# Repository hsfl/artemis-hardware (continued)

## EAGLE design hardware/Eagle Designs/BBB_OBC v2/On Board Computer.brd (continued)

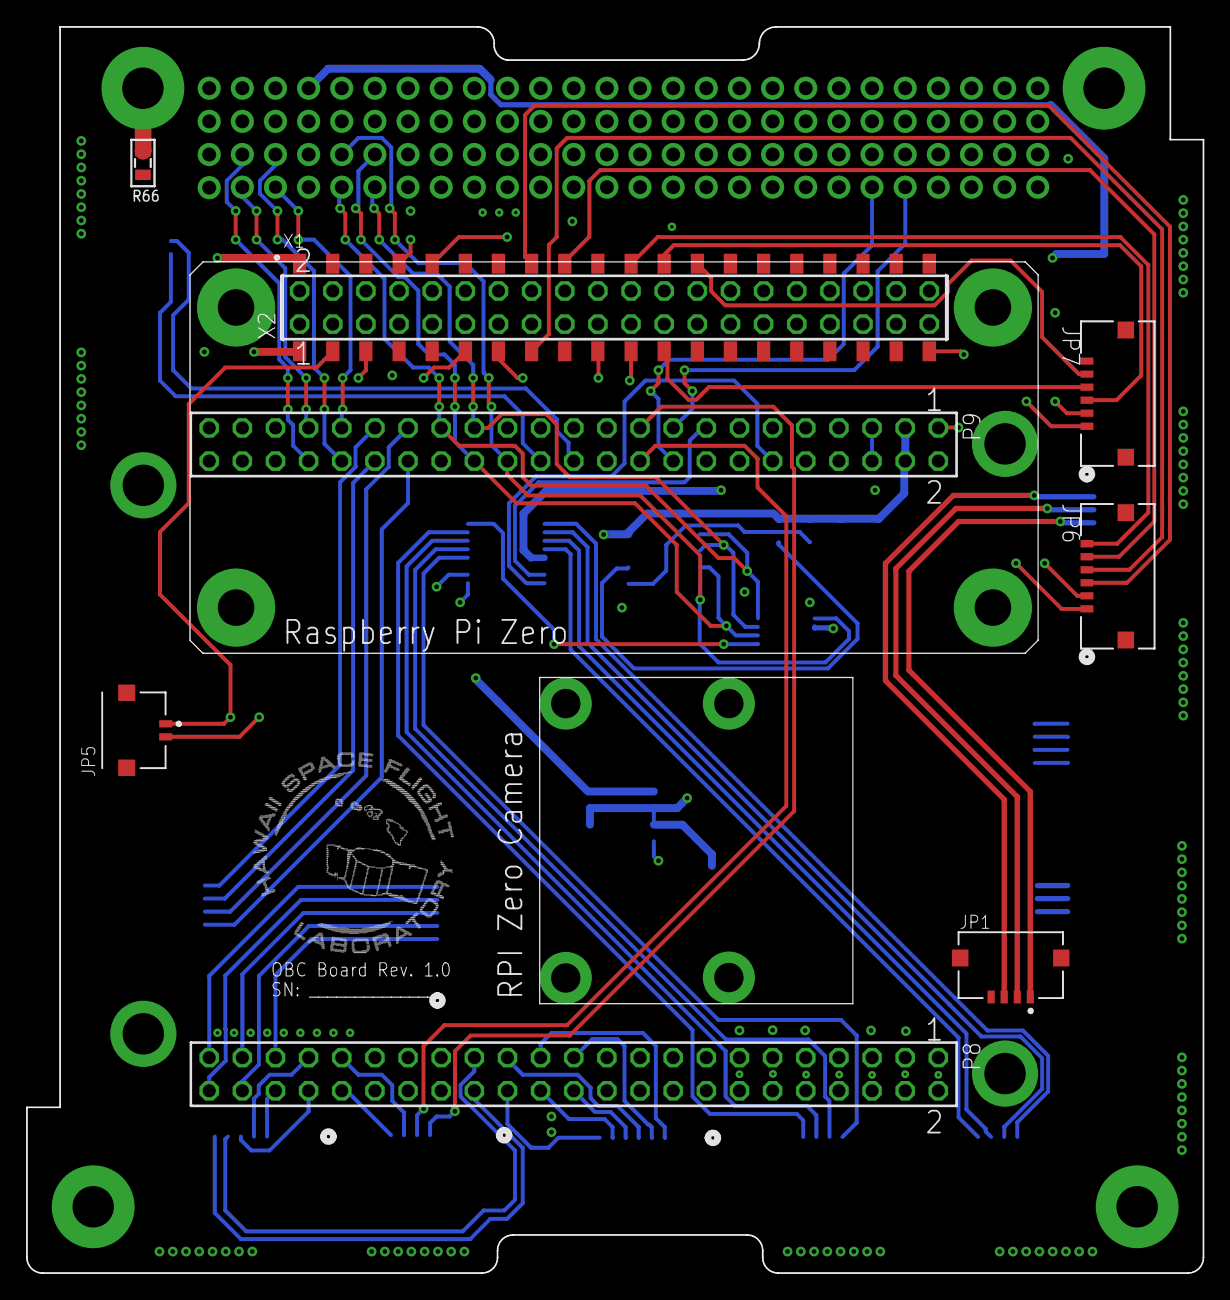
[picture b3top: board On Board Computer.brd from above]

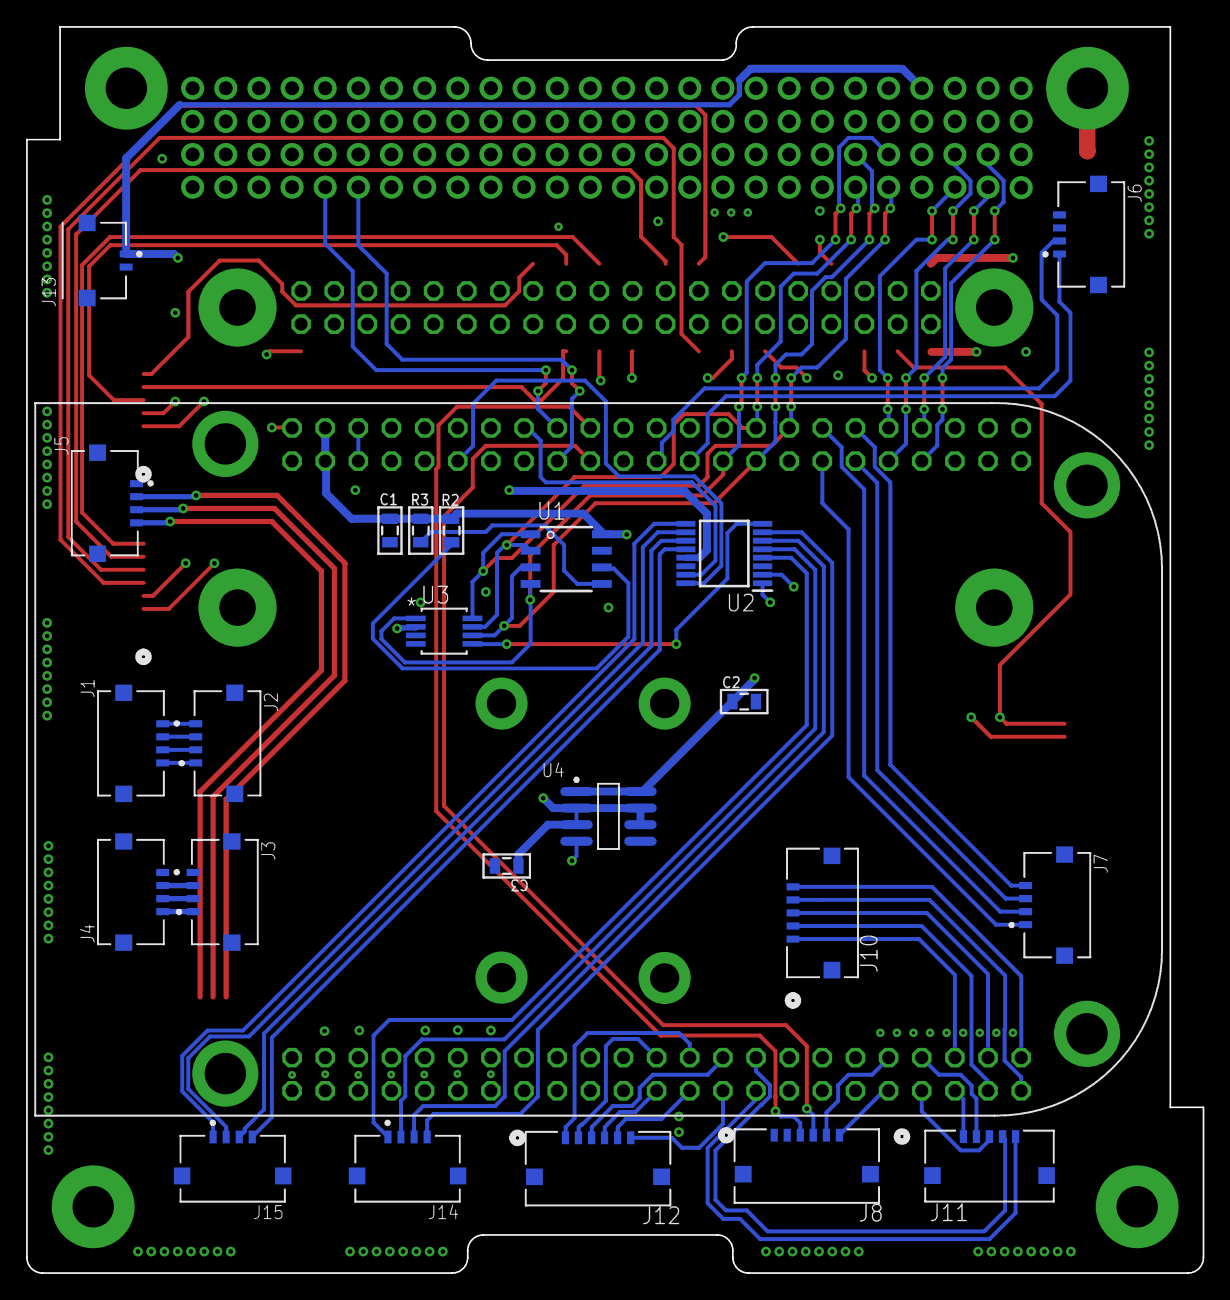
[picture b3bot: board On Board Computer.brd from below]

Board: 4 copper layers, 90.2 x 95.5 mm, 33 parts (23 on the bottom side), 85 nets.

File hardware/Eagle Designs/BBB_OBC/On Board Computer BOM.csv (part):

"Part";"Value";"Device";"Package";"Description";"AUTOMOTIVE";"BUILT_BY";"CENTROID_NOT_SPECIFIED";"CONN_GENDER";"CONN_ORIENTATION";"CONTACT_MATERIAL";"COPYRIGHT";"CURRENT_RATING";"DATASHEET";"DESCRIPTION";"DEVICE_CLASS_L1";"DEVICE_CLASS_L2";"DEVICE_CLASS_L3";"DIGIKEY_DESCRIPTION";"DIGIKEY_PART_NUMBER";"FOOTPRINT_URL";"FOOTPRINT_VARIANT_NAME_0";"HEIGHT";"LEAD_FREE";"MANUFACTURER_NAME";"MANUFACTURER_PART_NUMBER";"MF";"MFG_PACKAGE_IDENT";"MFG_PACKAGE_IDENT_DATE";"MFG_PACKAGE_IDENT_REV";"MOUSER_PART_NUMBER";"MOUSER_PRICE-STOCK";"MPN";"NUMBER_OF_CONTACTS";"NUMBER_OF_ROWS";"OC_FARNELL";"OC_NEWARK";"PACKAGE";"PITCH";"PREFIX";"ROHS";"SOURCELIBRARY";"TEMPERATURE_RANGE_HIGH";"TEMPERATURE_RANGE_LOW";"VENDOR";"VERIFICATION_VERSION";"VOLTAGE_RATING";
"C1";"0.1uF";"CAP0805";"0805";"Capacitor";"";"";"";"";"";"";"";"";"";"";"";"";"";"";"";"";"";"";"";"";"";"";"";"";"";"";"";"";"";"";"";"";"";"";"";"";"";"";"";"";"";"";
"H1";"PC104_WCONN";"PC104_WCONN";"PC104_WCONN";"";"";"";"";"";"";"";"";"";"";"";"";"";"";"";"";"";"";"";"";"";"";"";"";"";"";"";"";"";"";"";"";"";"";"";"";"";"";"";"";"";"";"";
"J1";"MOLEX_503763-0491MOLEX_503763-0491_0_0";"MOLEX_503763-0491MOLEX_503763-0491_0_0";"MOLEX_503763-0491_0";"Wire-To-Board Connector, Pico-Lock 503763 Series, Surface Mount, Header, 4 Contacts, 1 mm";"No";"";"No";"Male";"Right Angle";"Gold,Nickel";"";"1.5A";"https://www.molex.com/webdocs/datasheets/pdf/en-us/503763049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";"";"Connectors";"Headers and Wire Housings";"unset";"CONN HEADER 1MM R/A 4CKT";"WM10655CT-ND";"https://www.molex.com/pdm_docs/sd/5037630491_sd.pdf";"Recommended_Land_Pattern";"1.7mm";"Yes";"";"";"Molex";"503763-0491";"0";"0";"538-503763-0491";"";"503763-0491";"4";"1";"";"";"HDR4";"1mm";"J";"Yes";"";"+105°C";"-40°C";"";"0.0.0.1";"150V";
"J2";"MOLEX_503763-0491MOLEX_503763-0491_0_0";"MOLEX_503763-0491MOLEX_503763-0491_0_0";"MOLEX_503763-0491_0";"Wire-To-Board Connector, Pico-Lock 503763 Series, Surface Mount, Header, 4 Contacts, 1 mm";"No";"";"No";"Male";"Right Angle";"Gold,Nickel";"";"1.5A";"https://www.molex.com/webdocs/datasheets/pdf/en-us/503763049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";"";"Connectors";"Headers and Wire Housings";"unset";"CONN HEADER 1MM R/A 4CKT";"WM10655CT-ND";"https://www.molex.com/pdm_docs/sd/5037630491_sd.pdf";"Recommended_Land_Pattern";"1.7mm";"Yes";"";"";"Molex";"503763-0491";"0";"0";"538-503763-0491";"";"503763-0491";"4";"1";"";"";"HDR4";"1mm";"J";"Yes";"";"+105°C";"-40°C";"";"0.0.0.1";"150V";
"J3";"503763-0591";"503763-0591";"CONN_5037630591_MOL";"";"";"EMA_Cory";"";"";"";"";"Copyright (C) 2018 Accelerated Designs. All rights reserved";"";"https://www.molex.com/pdm_docs/sd/5037630591_sd.pdf";"";"";"";"";"";"";"";"";"";"";"";"503763-0591";"";"";"";"";"";"";"";"";"";"";"";"";"";"";"";"Add_to_database_2020-12-14";"";"";"Molex Connector Corporation";"";"";
"J4";"503763-0591";"503763-0591";"CONN_5037630591_MOL";"";"";"EMA_Cory";"";"";"";"";"Copyright (C) 2018 Accelerated Designs. All rights reserved";"";"https://www.molex.com/pdm_docs/sd/5037630591_sd.pdf";"";"";"";"";"";"";"";"";"";"";"";"503763-0591";"";"";"";"";"";"";"";"";"";"";"";"";"";"";"";"Add_to_database_2020-12-14";"";"";"Molex Connector Corporation";"";"";
"J5";"MOLEX_503763-0491MOLEX_503763-0491_0_0";"MOLEX_503763-0491MOLEX_503763-0491_0_0";"MOLEX_503763-0491_0";"Wire-To-Board Connector, Pico-Lock 503763 Series, Surface Mount, Header, 4 Contacts, 1 mm";"No";"";"No";"Male";"Right Angle";"Gold,Nickel";"";"1.5A";"https://www.molex.com/webdocs/datasheets/pdf/en-us/503763049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";"";"Connectors";"Headers and Wire Housings";"unset";"CONN HEADER 1MM R/A 4CKT";"WM10655CT-ND";"https://www.molex.com/pdm_docs/sd/5037630491_sd.pdf";"Recommended_Land_Pattern";"1.7mm";"Yes";"";"";"Molex";"503763-0491";"0";"0";"538-503763-0491";"";"503763-0491";"4";"1";"";"";"HDR4";"1mm";"J";"Yes";"";"+105°C";"-40°C";"";"0.0.0.1";"150V";
"J6";"MOLEX_503763-0491MOLEX_503763-0491_0_0";"MOLEX_503763-0491MOLEX_503763-0491_0_0";"MOLEX_503763-0491_0";"Wire-To-Board Connector, Pico-Lock 503763 Series, Surface Mount, Header, 4 Contacts, 1 mm";"No";"";"No";"Male";"Right Angle";"Gold,Nickel";"";"1.5A";"https://www.molex.com/webdocs/datasheets/pdf/en-us/503763049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";"";"Connectors";"Headers and Wire Housings";"unset";"CONN HEADER 1MM R/A 4CKT";"WM10655CT-ND";"https://www.molex.com/pdm_docs/sd/5037630491_sd.pdf";"Recommended_Land_Pattern";"1.7mm";"Yes";"";"";"Molex";"503763-0491";"0";"0";"538-503763-0491";"";"503763-0491";"4";"1";"";"";"HDR4";"1mm";"J";"Yes";"";"+105°C";"-40°C";"";"0.0.0.1";"150V";
"J7";"MOLEX_503763-0491MOLEX_503763-0491_0_0";"MOLEX_503763-0491MOLEX_503763-0491_0_0";"MOLEX_503763-0491_0";"Wire-To-Board Connector, Pico-Lock 503763 Series, Surface Mount, Header, 4 Contacts, 1 mm";"No";"";"No";"Male";"Right Angle";"Gold,Nickel";"";"1.5A";"https://www.molex.com/webdocs/datasheets/pdf/en-us/503763049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";"";"Connectors";"Headers and Wire Housings";"unset";"CONN HEADER 1MM R/A 4CKT";"WM10655CT-ND";"https://www.molex.com/pdm_docs/sd/5037630491_sd.pdf";"Recommended_Land_Pattern";"1.7mm";"Yes";"";"";"Molex";"503763-0491";"0";"0";"538-503763-0491";"";"503763-0491";"4";"1";"";"";"HDR4";"1mm";"J";"Yes";"";"+105°C";"-40°C";"";"0.0.0.1";"150V";
"J8";"503763-0691";"503763-0691";"CONN_503763-0691_MOL";"";"";"EMA_Cory";"";"";"";"";"Copyright (C) 2018 Accelerated Designs. All rights reserved";"";"https://www.digikey.com/products/en?keywords=503763-0691";"";"";"";"";"";"";"";"";"";"";"";"503763-0691";"";"";"";"";"";"";"";"";"";"";"";"";"";"";"";"Molex_2020-01-22";"";"";"Molex Connector Corporation";"";"";
"J9";"MOLEX_503763-0491MOLEX_503763-0491_0_0";"MOLEX_503763-0491MOLEX_503763-0491_0_0";"MOLEX_503763-0491_0";"Wire-To-Board Connector, Pico-Lock 503763 Series, Surface Mount, Header, 4 Contacts, 1 mm";"No";"";"No";"Male";"Right Angle";"Gold,Nickel";"";"1.5A";"https://www.molex.com/webdocs/datasheets/pdf/en-us/503763049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";"";"Connectors";"Headers and Wire Housings";"unset";"CONN HEADER 1MM R/A 4CKT";"WM10655CT-ND";"https://www.molex.com/pdm_docs/sd/5037630491_sd.pdf";"Recommended_Land_Pattern";"1.7mm";"Yes";"";"";"Molex";"503763-0491";"0";"0";"538-503763-0491";"";"503763-0491";"4";"1";"";"";"HDR4";"1mm";"J";"Yes";"";"+105°C";"-40°C";"";"0.0.0.1";"150V";
"J10";"503763-0591";"503763-0591";"CONN_5037630591_MOL";"";"";"EMA_Cory";"";"";"";"";"Copyright (C) 2018 Accelerated Designs. All rights reserved";"";"https://www.molex.com/pdm_docs/sd/5037630591_sd.pdf";"";"";"";"";"";"";"";"";"";"";"";"503763-0591";"";"";"";"";"";"";"";"";"";"";"";"";"";"";"";"Add_to_database_2020-12-14";"";"";"Molex Connector Corporation";"";"";
"J11";"503763-0591";"503763-0591";"CONN_5037630591_MOL";"";"";"EMA_Cory";"";"";"";"";"Copyright (C) 2018 Accelerated Designs. All rights reserved";"";"https://www.molex.com/pdm_docs/sd/5037630591_sd.pdf";"";"";"";"";"";"";"";"";"";"";"";"503763-0591";"";"";"";"";"";"";"";"";"";"";"";"";"";"";"";"Add_to_database_2020-12-14";"";"";"Molex Connector Corporation";"";"";
"J12";"503763-0691";"503763-0691";"CONN_503763-0691_MOL";"";"";"EMA_Cory";"";"";"";"";"Copyright (C) 2018 Accelerated Designs. All rights reserved";"";"https://www.digikey.com/products/en?keywords=503763-0691";"";"";"";"";"";"";"";"";"";"";"";"503763-0691";"";"";"";"";"";"";"";"";"";"";"";"";"";"";"";"Molex_2020-01-22";"";"";"Molex Connector Corporation";"";"";
"J13";"MOLEX_503763-0291MOLEX_503763-0291_0_0";"MOLEX_503763-0291MOLEX_503763-0291_0_0";"MOLEX_503763-0291_0";"2 Positions Header Connector 0.039" (1.00mm) Surface Mount, Right Angle Gold";"";"";"No";"";"";"";"";"";"http://www.molex.com/pdm_docs/sd/5037630291_sd.pdf";"";"";"";"";"CONN HEADER 1MM R/A 2CKT";"WM10654CT-ND";"";"";"";"yes";"";"";"Molex";"";"";"";"538-503763-0291";"";"503763-0291";"";"";"";"";"HDR02";"";"J";"yes";"";"+105°C";"-40°C";"";"";"";
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
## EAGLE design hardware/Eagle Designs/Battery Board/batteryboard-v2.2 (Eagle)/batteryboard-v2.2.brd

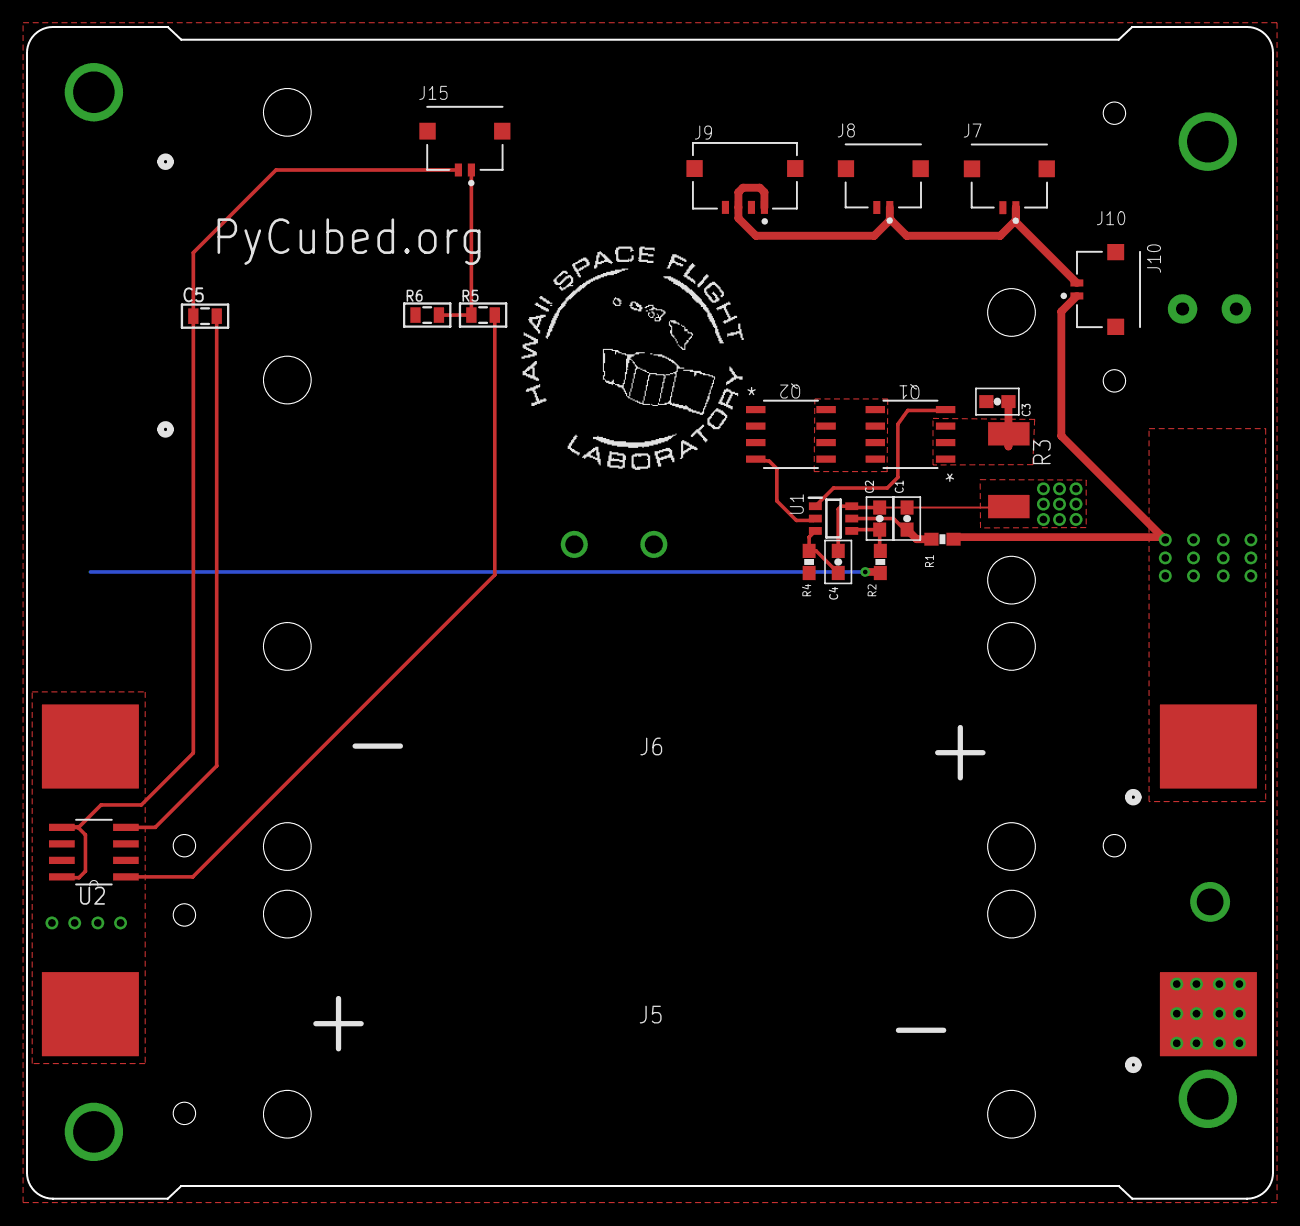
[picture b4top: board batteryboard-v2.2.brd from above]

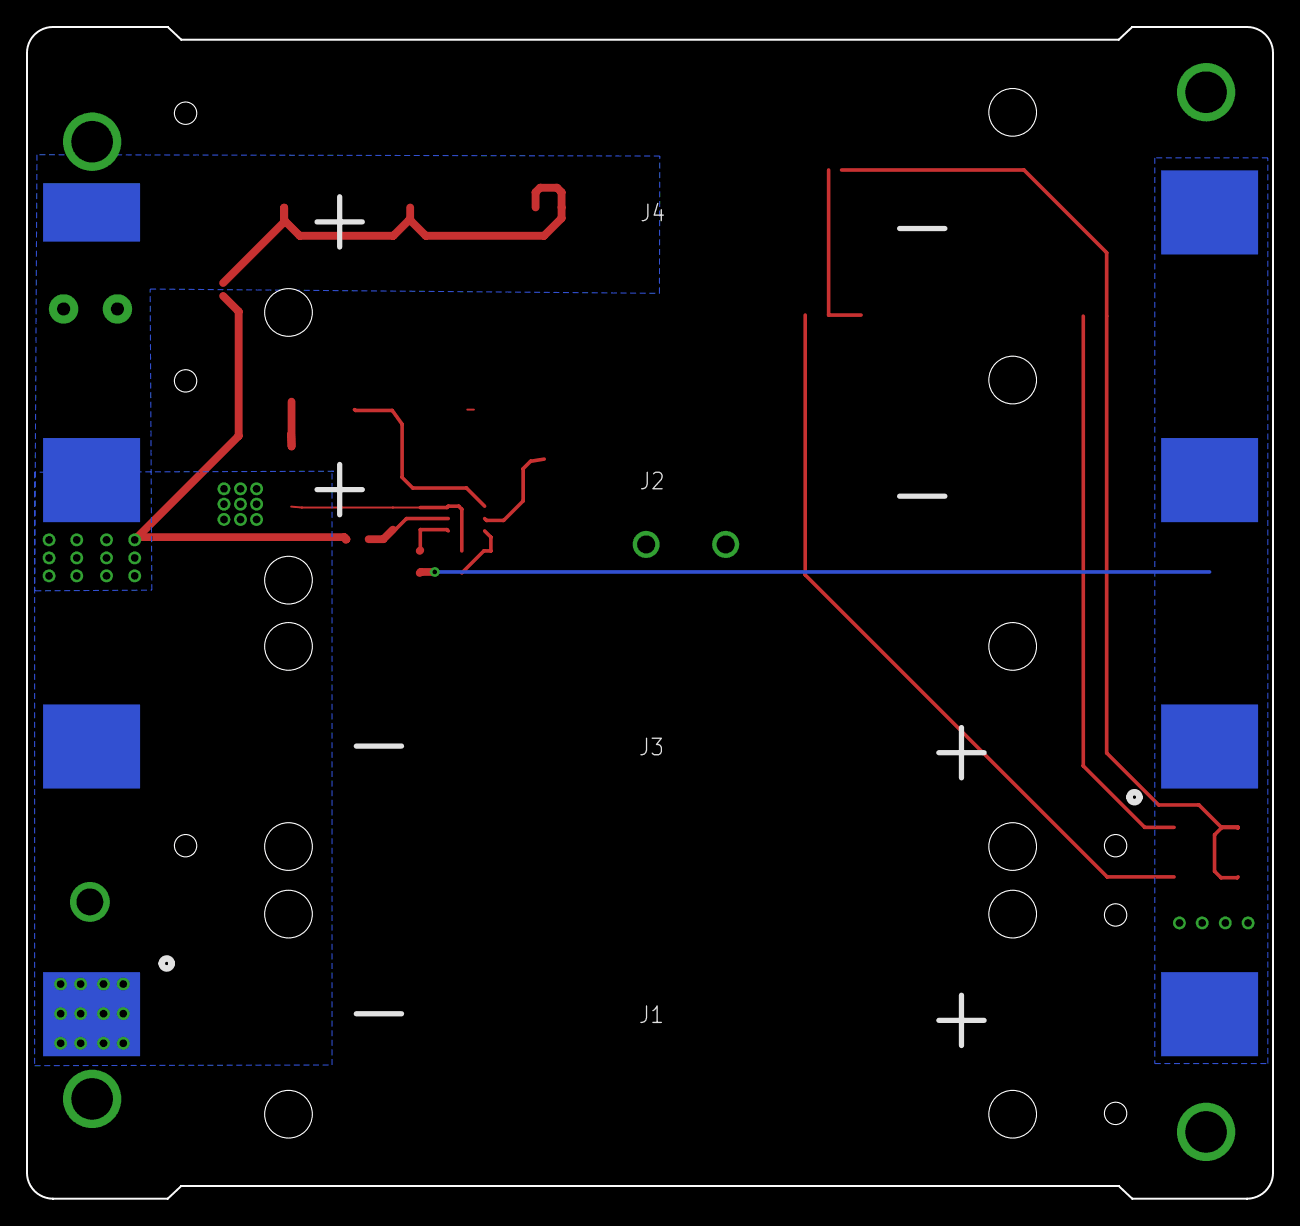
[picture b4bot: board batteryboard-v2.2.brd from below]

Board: 2 copper layers, 95.9 x 90.2 mm, 27 parts (4 on the bottom side), 16 nets.

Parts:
C1, C2, C3, C4: 0.1u; 0603-CAP
C5: 0.1u; 0805
J1, J2, J3, J5, J6: 1042; 1042_KEY
J4: 1042_SMALLPAD; 1042_KEY_SMALLPAD
J7, J8, J10, J15: MOLEX_503763-0291MOLEX_503763-0291_0_0; MOLEX_503763-0291_0
J9: MOLEX_503763-0491MOLEX_503763-0491_0_0; MOLEX_503763-0491_0
Q1, Q2: IRF7458TRPBF; SO-8_IRF7458_3P9X4P9_INF
R1, R2: 330; 0603-RES
R3: 0.01; R2512
R4: 1k; 0603-RES
R5: 45.3k; 0805
R6: 10k; 0805
U1: R5460N233AF-TR-FE; SOT95P280X140-6N
U2: TMP36GSZ; SOIC127P600X175-8N
U$1: PC104_HOLES

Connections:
B-: C1.1, C2.1, C4.1, J1.1, J3.1, J5.1, R3.2, U1.6
BM: J5.2, J6.1
BM+: J1.2, J2.1, J3.2, J4.1, R2.1
CONN1: J7.1, J8.1, J9.1, J9.3, J10.2
unnamed: R5.2, U2.1
unnamed: C3.2, Q1.1, Q1.2, Q1.3, R3.1
unnamed: C4.2, R4.2, U1.3
unnamed: Q1.5, Q1.6, Q1.7, Q1.8, Q2.5, Q2.6, Q2.7, Q2.8
PACK+: J2.2, J4.2, J6.2, J10.1, R1.1
PACK-: C3.1, C5.2, J7.2, J7.3, J7.4, J8.2, J8.3, J8.4, J9.2, J9.4, J9.5, J9.6, J10.3, J10.4, J15.3, J15.4, Q2.1, Q2.2, Q2.3, R4.1, R6.1, U2.4
Q1CONN: Q1.4, U1.1
Q2CONN: Q2.4, U1.2
R2: C2.2, R2.2, U1.4
VDD: C1.2, R1.2, U1.5
VOUT: J15.1, R5.1, R6.2
VS: C5.1, J15.2, U2.5, U2.8
